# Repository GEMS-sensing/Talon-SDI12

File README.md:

<!--  -->

# Talon-SDI12
Talon daughterboard for [Flight data logger](https://github.com/GEMS-sensing/DFM_-_Flight?tab=readme-ov-file). Designed to interface with [Kestrel](https://github.com/GEMS-sensing/Project-Kestrel) main board. This board is designed to provide data logger with support to interface with [SDI-12 communication standard](https://www.sdi-12.org/current_specification/SDI-12%20Specification%201.4%20February%2020%202023.pdf) for environmental sensors.

# Repo Roadmap
#### [Documents](Documents/) 

General document and image storage for repo and README

#### [Hardware](Hardware/)

Current board files (Eagle), Bill of Materials (BoM), and other design documents

#### [Production](Production/)

Contains the various Gerber and pick and place files required to have the Printed Circuit Boards (PCBs) manufactured or populated 

#### [Software](Software/)

The software associated with the piece of hardware, this is usually diagnostic software used for verifying or investigating the hardware

<!-- #### [Mechanical](Mechanical/)

Mechanical design files and assembly documents -->

<!-- #### [Testing](Testing/)

Scripts and results from the testing process and development process. Contains more detailed information about documented issues among other testing. 
 -->

## Overview
* **Type:** Talon
* **Interfaces:** SDI-12
* **Release Version:** v1.4 - 2022/04/25

<!--  -->

## Features
### On-Board
* SDI-12 ports (x3)
* Dedicated Apogee sensor port (x1)
	* Supports SDI-12 communication and analog voltage input
	* Supports [Apogee pinout standard](https://www.apogeeinstruments.com/apogee-wiring-guide/)
* Port level current limit
	* Custom designed automatic current limit 
	* support for current and voltage measurement for each port
* Data and power control for each port
* Loopback support to perform SDI-12 communication diagnostics 
* EEPROM with UUID built in - can store additional values defined by firmware to track offsets, etc
* ESD protected inputs

<!-- ### Interface
* I<sup>2</sup>C
* M12 circular connector  -->

<!-- <picture>
  <source media="(prefers-color-scheme: dark)" srcset="Documents/Pinout_LIGHT.png">
  
</picture> -->

<!-- ## Specifications
* **Voltage - Supply:** 3.3V
* **Voltage - Logic:** 3.3V
* **Input Current (Avg, 1s period): 30.95&mu;A @ 3.3V**
* **Input Current (Avg, 5s period): 107.43&mu;A @ 3.3V**
* **Input Current (Max): 0.45mA @ 3.3V**

#### Sensor
**Temperature** [^1]
* Range: -40 ~ 125°C 
* Accuracy: &plusmn; 0.2°C
* Repeatability: &plusmn; 0.04°C

**Pressure** [^2]
* Range: 300 ~ 1200 hPa  
* Accuracy: &plusmn; 1 hPa
* Repeatability: &plusmn; 0.06 hPa

**Humidity** [^1]
* Range: 0 ~ 100%
* Accuracy: &plusmn; 2%
* Repeatability: 0.08%

[^1]: [SHT31 Datasheet](https://sensirion.com/media/documents/213E6A3B/63A5A569/Datasheet_SHT3x_DIS.pdf)
[^2]: [DPS368 Datasheet](https://www.infineon.com/dgdl/Infineon-DPS368-DS-v01_00-EN.pdf?fileId=5546d46269e1c019016a0c45105d4b40) -->

<!-- ## Version History

`v0.0` - Initial primal version with screw terminal

`v0.1` - Initial 'hard mount' version, using M12 connector

`v1.0` - Removed pullup select[^3], added logic level buffer and voltage reg on input

`v1.1` - Moved via away from connector pads to prevent bridging when soldering 

`v2.0` - Fixed issue with address select jumper[^3] -->

<!-- ## Jumper Settings 

> [!IMPORTANT]
> Jumper settings valid for version `v2.0` and beyond[^3]

[^3]: See Errata

**Configuration Jumpers**
| Jumper | Purpose | Open | Closed | Default | 
| ------ | ------- | ---------- | ---------- | ----- | 
| `JP1` | I<sup>2</sup>C Address Select | Base Address<sup>&dagger;</sup> | Alt Address<sup>&Dagger;</sup> | Open |

&dagger; SHT31 = `0x44`, DPS368 = `0x76`

&Dagger; SHT31 = `0x44`, DPS368 = `0x77`
 -->

## Known Issues/Errata

None
<!-- #### Solder Jumper Stencil

**Version Affected:** All

**Issue:** Solar input does not support very low impedance sources (e.g. lead acid battery) - see details in issue [#20](https://github.com/GEMS-sensing/Project-Kestrel/issues/20)

**Workaround:** 

* Avoid use of low impedance batteries for input
* Include series impedance to prevent current spikes (not desirable)
* Perform board patch described in issue [#20](https://github.com/GEMS-sensing/Project-Kestrel/issues/20) -->

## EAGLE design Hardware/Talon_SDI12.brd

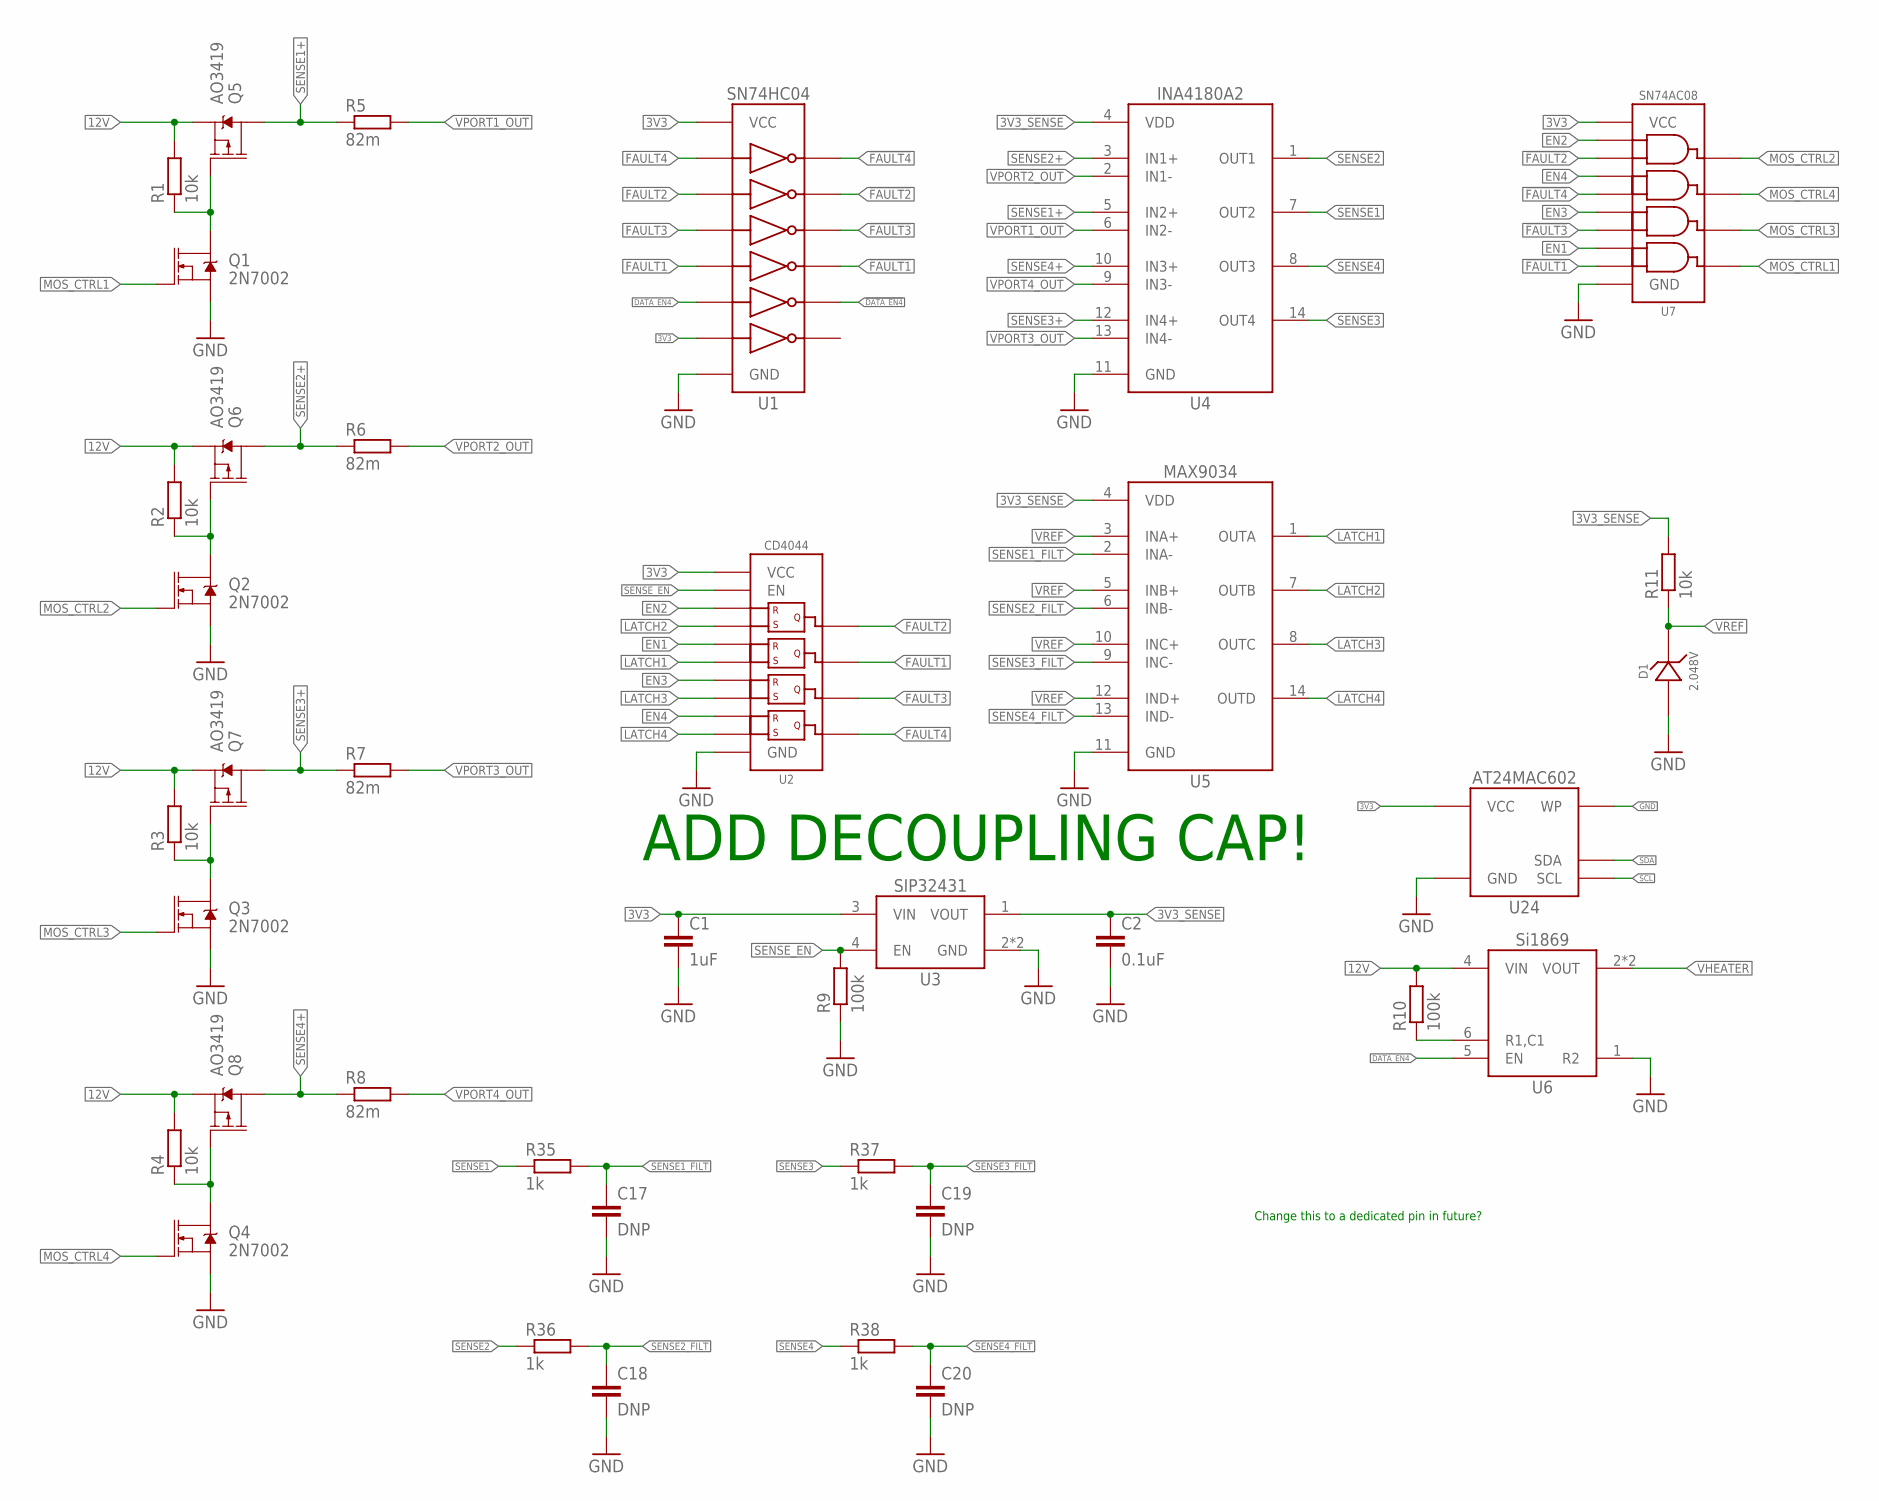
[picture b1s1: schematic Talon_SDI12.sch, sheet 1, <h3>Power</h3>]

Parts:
C1: 1uF; C0603
C2: 0.1uF; C0402
C17, C18, C19, C20: DNP; C0402; MPN DNP; DIGIKEY DNP
D1: 2.048V; SOT23-3
Q1, Q2, Q3, Q4: 2N7002; SOT23-3
Q5, Q6, Q7, Q8: AO3419; SOT23-3
R1, R2, R3, R4, R11: 10k; R0402
R5, R6, R7, R8: 82m; R0603
R9, R10: 100k; R0402
R35, R36, R37, R38: 1k; R0402
U1: SN74HC04; TSSOP14
U2: CD4044; TSSOP16
U3: SIP32431TDFN; TDFN_4
U4: INA4180A2; TSSOP14
U5: MAX9034TSSOP; TSSOP14
U6: SI1869; SC-70_6
U7: SN74AC08; TSSOP14
U24: AT24MAC602SOT23; SOT23-5

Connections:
3V3: C1.1, U1.13 (A6), U1.14 (VCC), U2.16 (VCC), U3.3 (VIN), U7.14 (VCC), U24.4 (VCC); also elsewhere on the board
3V3_SENSE: C2.1, R11.2, U3.1 (VOUT), U4.4 (VDD), U5.4 (VDD)
12V: Q5.2 (S), Q6.2 (S), Q7.2 (S), Q8.2 (S), R1.2, R2.2, R3.2, R4.2, R10.2, U6.4 (VIN); also elsewhere on the board
!DATA_EN4: U1.10 (Y5); also elsewhere on the board
!FAULT1: U1.8 (Y4), U7.13 (B4)
!FAULT2: U1.4 (Y2), U7.2 (B1)
!FAULT3: U1.6 (Y3), U7.10 (B3)
!FAULT4: U1.2 (Y1), U7.5 (B2)
DATA_EN4: U1.11 (A5), U6.5 (EN); also elsewhere on the board
EN1: U2.6 (R2), U7.12 (A4); also elsewhere on the board
EN2: U2.4 (R1), U7.1 (A1); also elsewhere on the board
EN3: U2.12 (R3), U7.9 (A3); also elsewhere on the board
EN4: U2.14 (R4), U7.4 (A2); also elsewhere on the board
FAULT1: U1.9 (A4), U2.9 (Q2); also elsewhere on the board
FAULT2: U1.3 (A2), U2.13 (Q1); also elsewhere on the board
FAULT3: U1.5 (A3), U2.10 (Q3); also elsewhere on the board
FAULT4: U1.1 (A1), U2.1 (Q4); also elsewhere on the board
GND: C1.2, C2.2, C17.2, C18.2, C19.2, C20.2, D1.2 (A), Q1.2 (S), Q2.2 (S), Q3.2 (S), Q4.2 (S), R9.1, U1.7 (GND), U2.8 (GND), U3.2 (GND), U3.EP (GND), U4.11 (GND), U5.11 (GND), U6.1 (R2), U7.7 (GND), U24.2 (GND), U24.5 (WP); also elsewhere on the board
LATCH1: U2.7 (S2), U5.1 (OUTA)
LATCH2: U2.3 (S1), U5.7 (OUTB)
LATCH3: U2.11 (S3), U5.8 (OUTC)
LATCH4: U2.15 (S4), U5.14 (OUTD)
MOS_CTRL1: Q1.1 (G), U7.11 (Y4)
MOS_CTRL2: Q2.1 (G), U7.3 (Y1)
MOS_CTRL3: Q3.1 (G), U7.8 (Y3)
MOS_CTRL4: Q4.1 (G), U7.6 (Y2)
unnamed: Q2.3 (D), Q6.1 (G), R2.1
unnamed: Q1.3 (D), Q5.1 (G), R1.1
unnamed: Q3.3 (D), Q7.1 (G), R3.1
unnamed: Q4.3 (D), Q8.1 (G), R4.1
unnamed: R10.1, U6.6 (R1,C1)
SCL: U24.1 (SCL); also elsewhere on the board
SDA: U24.3 (SDA); also elsewhere on the board
SENSE1: R35.1, U4.7 (OUT2); also elsewhere on the board
SENSE1+: Q5.3 (D), R5.1, U4.5 (IN2+)
SENSE1_FILT: C17.1, R35.2, U5.2 (INA-)
SENSE2: R36.1, U4.1 (OUT1); also elsewhere on the board
SENSE2+: Q6.3 (D), R6.1, U4.3 (IN1+)
SENSE2_FILT: C18.1, R36.2, U5.6 (INB-)
SENSE3: R37.1, U4.14 (OUT4); also elsewhere on the board
SENSE3+: Q7.3 (D), R7.1, U4.12 (IN4+)
SENSE3_FILT: C19.1, R37.2, U5.9 (INC-)
SENSE4: R38.1, U4.8 (OUT3); also elsewhere on the board
SENSE4+: Q8.3 (D), R8.1, U4.10 (IN3+)
SENSE4_FILT: C20.1, R38.2, U5.13 (IND-)
SENSE_EN: R9.2, U2.5 (EN), U3.4 (EN); also elsewhere on the board
VHEATER: U6.2 (VOUT), U6.3 (VOUT); also elsewhere on the board
VPORT1_OUT: R5.2, U4.6 (IN2-); also elsewhere on the board
VPORT2_OUT: R6.2, U4.2 (IN1-); also elsewhere on the board
VPORT3_OUT: R7.2, U4.13 (IN4-); also elsewhere on the board
VPORT4_OUT: R8.2, U4.9 (IN3-); also elsewhere on the board
VREF: D1.1 (C), R11.1, U5.3 (INA+), U5.5 (INB+), U5.10 (INC+), U5.12 (IND+)

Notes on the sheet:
ADD DECOUPLING CAP!
Change this to a dedicated pin in future?

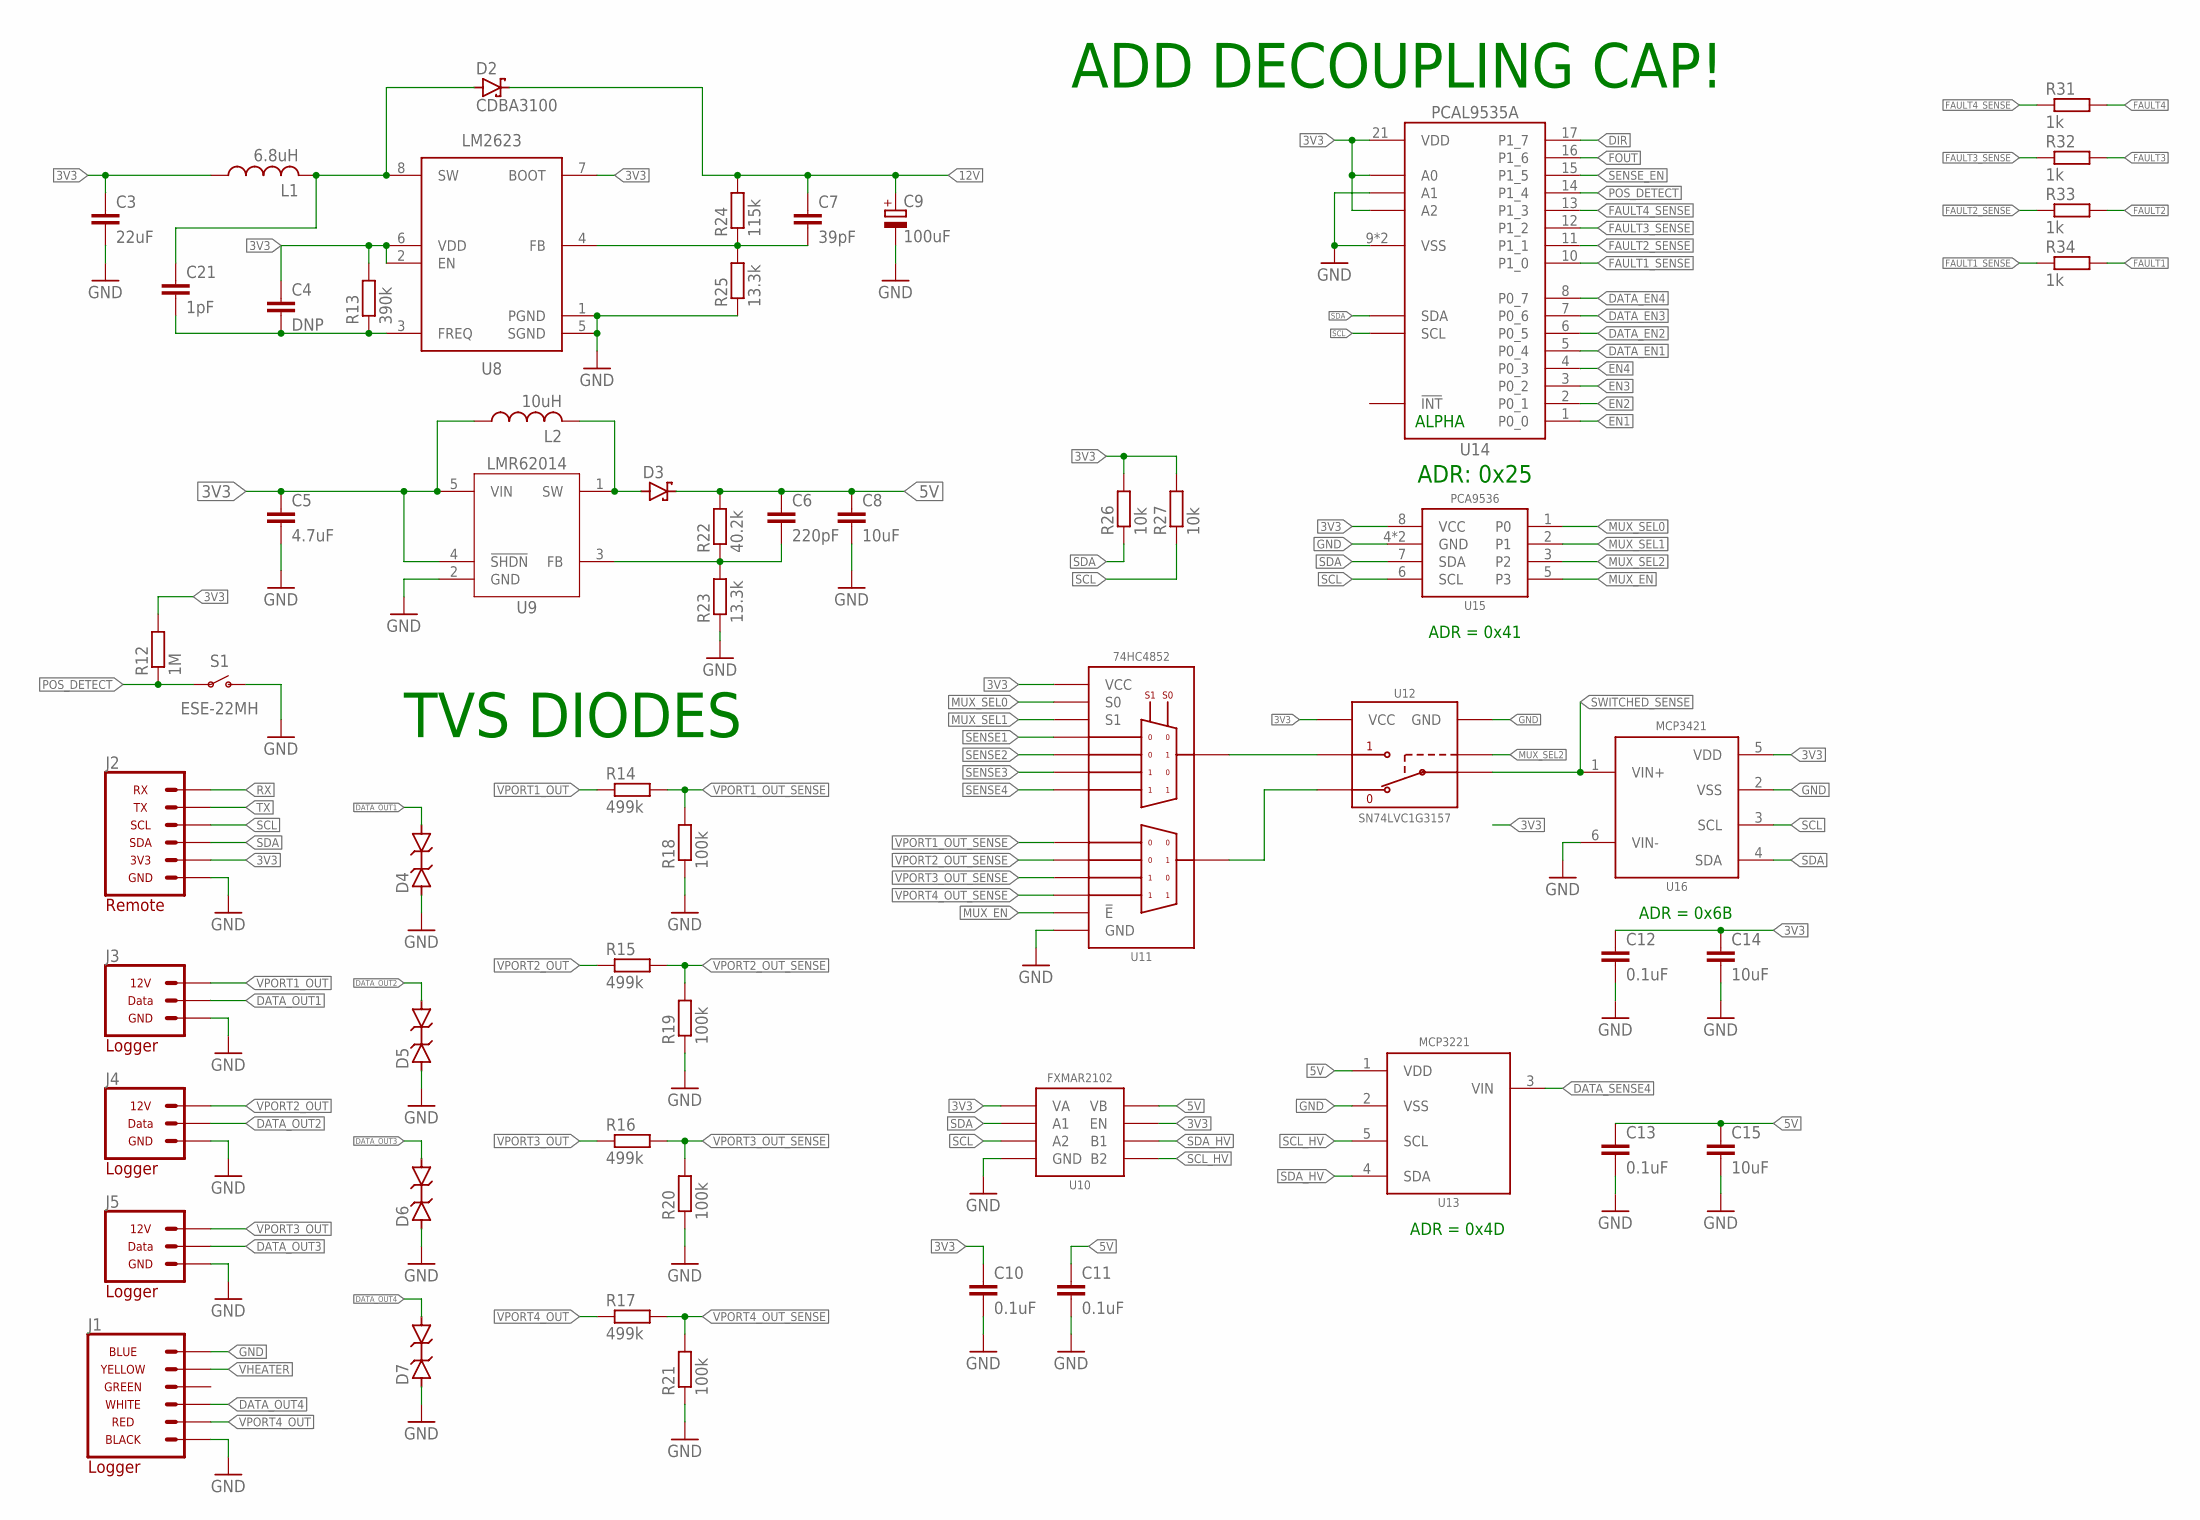
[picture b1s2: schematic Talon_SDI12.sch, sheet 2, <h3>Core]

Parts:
C3: 22uF; C0805
C4: DNP; C0402; MPN DNP; DIGIKEY DNP
C5: 4.7uF; C0805
C6: 220pF; C0603
C7: 39pF; C0402
C8: 10uF; C0805; MPN TMK212BBJ106KG-T; DIGIKEY 587-2985-1-ND
C9: 100uF; C2917; MPN 293D107X0016D2TE3; DIGIKEY 718-293D107X0016D2TE3CT-ND
C10, C11, C12, C13: 0.1uF; C0402
C14, C15: 10uF; C0805
C21: 1pF; C0402
D2: CDBA3100; DO214AC; MPN CDBA3100-HF; DIGIKEY 641-1747-1-ND
D3: DIODE_SCHOTTKYSOD-123; SOD-123; MPN MBR0520LT1G; DIGIKEY MBR0520LT1GOSCT-ND
D4, D5, D6, D7: 12V; D0402; MPN D12V0L1B2LP-7B; DIGIKEY D12V0L1B2LP-7BDICT-ND
J1: CONN_APOGEE_LOGGER; 1X06_M8_PHOENIX_1456022_BOARDLOCK
J2: CONN_TALON_REMOTE; 1X06_MICROLOCKPLUS
J3, J4, J5: CONN_SDI-12_LOGGERM8_TE_BOARDLOCK; 1X03_M8_TE_T40410_BOARDLOCK
L1: 6.8uH; WE-MAIA(4.1X4.1); MPN 78438357068; DIGIKEY 732-11744-1-ND
L2: 10uH; 1008; MPN 74438323100; DIGIKEY 732-4851-1-ND
R12: 1M; R0402
R13: 390k; R0603
R14, R15, R16, R17: 499k; R0603
R18, R19, R20, R21: 100k; R0402
R22: 40.2k; R0603
R23, R25: 13.3k; R0603
R24: 115k; R0603
R26, R27: 10k; R0402
R31, R32, R33, R34: 1k; R0402
S1: ESE-22MH
U8: LM2621; DGK_S-PDSO-G8; MPN LM2623AMM/NOPB; DIGIKEY LM2623AMM/NOPBCT-ND
U9: LMR62014SOT23; DBV0005A
U10: FXMAR2102UMLP; UQFN-8_1.4X1.2
U11: 74HC4852; VQFN-16
U12: SN74LVC1G3157SC70; DCK_R-PDSO-G6
U13: MCP3221; SOT23-5
U14: PCAL9535AQFN; QFN24
U15: PCA9536DFN; DFN_8_3X3
U16: MCP3421A3; SOT23-6L

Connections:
3V3: C3.1, C4.1, C5.1, C10.1, C12.1, C14.1, J2.2 (3V3), L1.P$1 (1), L2.1, R12.2, R13.2, R26.2, R27.2, U8.2 (EN), U8.6 (VDD), U8.7 (BOOT), U9.4 (!SHDN), U9.5 (VIN), U10.1 (VA), U10.5 (EN), U11.16 (VCC), U12.5 (VCC), U14.18 (A0), U14.21 (VDD), U14.24 (A2), U15.8 (VCC), U16.5 (VDD); also elsewhere on the board
5V: C6.1, C8.1, C11.1, C13.1, C15.1, D3.CAT (C), R22.2, U10.8 (VB), U13.1 (VDD); also elsewhere on the board
12V: C7.1, C9.+, D2.C, R24.2; also elsewhere on the board
DATA_EN1: U14.5 (P0_4); also elsewhere on the board
DATA_EN2: U14.6 (P0_5); also elsewhere on the board
DATA_EN3: U14.7 (P0_6); also elsewhere on the board
DATA_EN4: U14.8 (P0_7); also elsewhere on the board
DATA_OUT1: D4.2 (C), J3.4 (DATA); also elsewhere on the board
DATA_OUT2: D5.2 (C), J4.4 (DATA); also elsewhere on the board
DATA_OUT3: D6.2 (C), J5.4 (DATA); also elsewhere on the board
DATA_OUT4: D7.2 (C), J1.3; also elsewhere on the board
DATA_SENSE4: U13.3 (VIN); also elsewhere on the board
DIR: U14.17 (P1_7); also elsewhere on the board
EN1: U14.1 (P0_0); also elsewhere on the board
EN2: U14.2 (P0_1); also elsewhere on the board
EN3: U14.3 (P0_2); also elsewhere on the board
EN4: U14.4 (P0_3); also elsewhere on the board
FAULT1: R34.2; also elsewhere on the board
FAULT1_SENSE: R34.1, U14.10 (P1_0)
FAULT2: R33.2; also elsewhere on the board
FAULT2_SENSE: R33.1, U14.11 (P1_1)
FAULT3: R32.2; also elsewhere on the board
FAULT3_SENSE: R32.1, U14.12 (P1_2)
FAULT4: R31.2; also elsewhere on the board
FAULT4_SENSE: R31.1, U14.13 (P1_3)
FOUT: U14.16 (P1_6); also elsewhere on the board
GND: C3.2, C5.2, C8.2, C9.-, C10.2, C11.2, C12.2, C13.2, C14.2, C15.2, D4.1 (A), D5.1 (A), D6.1 (A), D7.1 (A), J1.1, J1.6, J2.1 (GND), J3.3 (GND), J4.3 (GND), J5.3 (GND), R18.1, R19.1, R20.1, R21.1, R23.1, R25.1, S1.1 (O), U8.1 (PGND), U8.5 (SGND), U9.2 (GND), U10.4 (GND), U11.8 (GND), U11.EP (GND), U12.2 (GND), U13.2 (VSS), U14.9 (VSS), U14.23 (A1), U14.EP (VSS), U15.4 (GND), U15.EP (GND), U16.2 (VSS), U16.6 (VIN-); also elsewhere on the board
MUX_EN: U11.6 (!E), U15.5 (P3); also elsewhere on the board
MUX_SEL0: U11.10 (S0), U15.1 (P0)
MUX_SEL1: U11.9 (S1), U15.2 (P1)
MUX_SEL2: U12.6 (S), U15.3 (P2)
unnamed: C4.2, C21.2, R13.1, U8.3 (FREQ)
unnamed: C21.1, D2.A, L1.P$2 (2), U8.8 (SW)
unnamed: C7.2, R24.1, R25.2, U8.4 (FB)
unnamed: C6.2, R22.1, R23.2, U9.3 (FB)
unnamed: U11.3 (2Z), U12.3 (B1)
unnamed: U11.13 (1Z), U12.1 (B2)
POS_DETECT: R12.1, S1.2, U14.14 (P1_4)
RX: J2.6 (RX); also elsewhere on the board
SCL: J2.4 (SCL), R27.1, U10.3 (A2), U14.19 (SCL), U15.6 (SCL), U16.3 (SCL); also elsewhere on the board
SCL_HV: U10.6 (B2), U13.5 (SCL)
SDA: J2.3 (SDA), R26.1, U10.2 (A1), U14.20 (SDA), U15.7 (SDA), U16.4 (SDA); also elsewhere on the board
SDA_HV: U10.7 (B1), U13.4 (SDA)
SENSE1: U11.12 (1Y0); also elsewhere on the board
SENSE2: U11.14 (1Y1); also elsewhere on the board
SENSE3: U11.15 (1Y2); also elsewhere on the board
SENSE4: U11.11 (1Y3); also elsewhere on the board
SENSE_EN: U14.15 (P1_5); also elsewhere on the board
SW1: D3.ANODE (A), L2.2, U9.1 (SW)
SWITCHED_SENSE: U12.4 (A), U16.1 (VIN+)
TX: J2.5 (TX); also elsewhere on the board
VHEATER: J1.5; also elsewhere on the board
VPORT1_OUT: J3.1 (12V), R14.1; also elsewhere on the board
VPORT1_OUT_SENSE: R14.2, R18.2, U11.1 (2Y0)
VPORT2_OUT: J4.1 (12V), R15.1; also elsewhere on the board
VPORT2_OUT_SENSE: R15.2, R19.2, U11.5 (2Y1)
VPORT3_OUT: J5.1 (12V), R16.1; also elsewhere on the board
VPORT3_OUT_SENSE: R16.2, R20.2, U11.2 (2Y2)
VPORT4_OUT: J1.2, R17.1; also elsewhere on the board
VPORT4_OUT_SENSE: R17.2, R21.2, U11.4 (2Y3)

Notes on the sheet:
ALPHA
ADD DECOUPLING CAP!
TVS DIODES
ADR: 0x25
ADR = 0x6B
ADR = 0x4D
ADR = 0x41

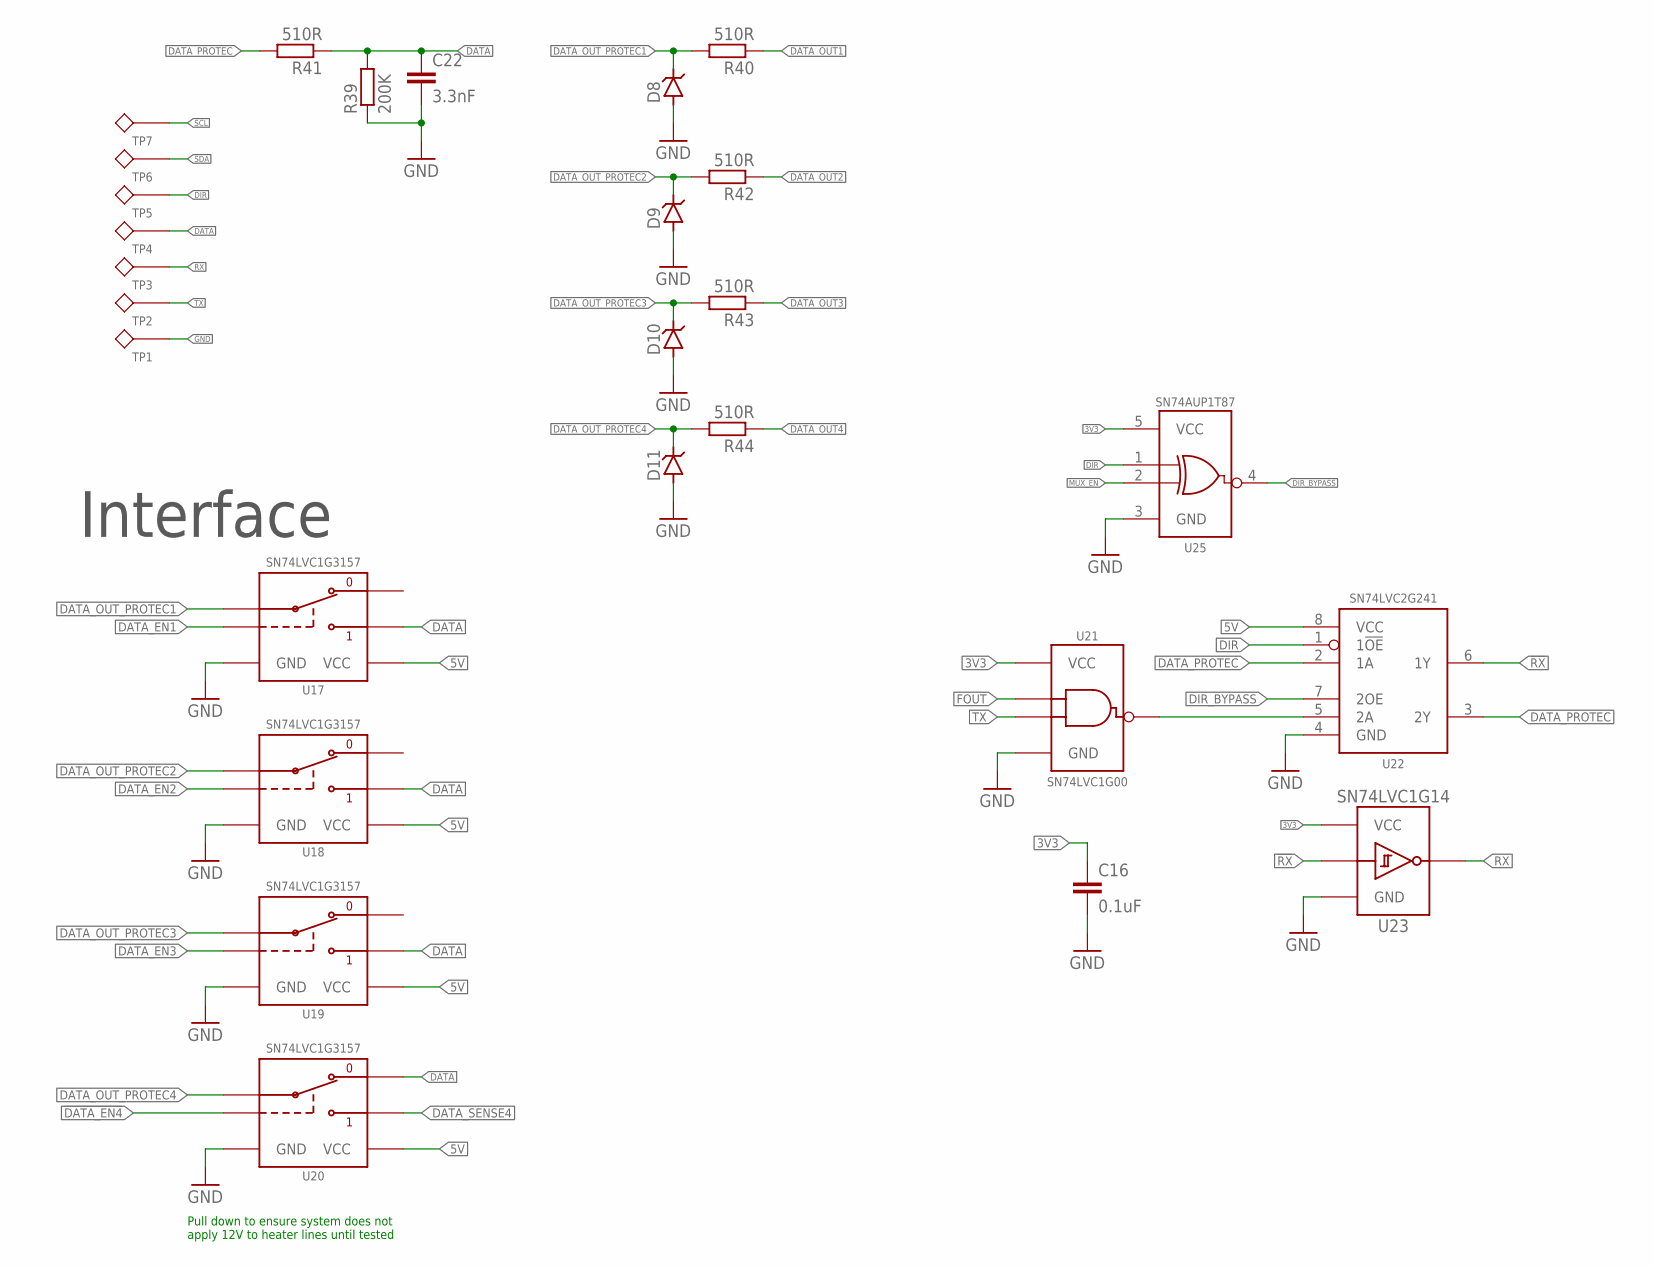
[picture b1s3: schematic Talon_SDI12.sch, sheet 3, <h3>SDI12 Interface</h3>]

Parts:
C16: 0.1uF; C0402
C22: 3.3nF; C0402
D8, D9, D10, D11: DIODE_ZENERSOD-323; SOD323-R; MPN BZX384B5V1-HE3-08; DIGIKEY BZX384B5V1-HE3-08GICT-ND
R39: 200K; R0402
R40, R41, R42, R43, R44: 510R; R0402
TP1, TP2, TP3, TP4, TP5, TP6, TP7: TESTPOINTRCU; TESTPOINT_0603
U17, U18, U19, U20: SN74LVC1G3157SC70; DCK_R-PDSO-G6
U21: SN74LVC1G00SC70; DCK_R-PDSO-G5
U22: SN74LVC2G241DCU; DCU_(R-PDSO-G8)
U23: SN74LVC1G14DCK; DCK_R-PDSO-G5
U25: SN74AUP1T87; DCK_R-PDSO-G5

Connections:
3V3: C16.1, U21.5 (VCC), U23.5 (VCC), U25.5 (VCC); also elsewhere on the board
5V: U17.5 (VCC), U18.5 (VCC), U19.5 (VCC), U20.5 (VCC), U22.8 (VCC); also elsewhere on the board
!DATA_EN4: U20.6 (S); also elsewhere on the board
!RX: U22.6 (1Y), U23.2 (A)
DATA: C22.1, R39.2, R41.1, TP4.1, U17.1 (B2), U18.1 (B2), U19.1 (B2), U20.3 (B1)
DATA_EN1: U17.6 (S); also elsewhere on the board
DATA_EN2: U18.6 (S); also elsewhere on the board
DATA_EN3: U19.6 (S); also elsewhere on the board
DATA_OUT1: R40.1; also elsewhere on the board
DATA_OUT2: R42.1; also elsewhere on the board
DATA_OUT3: R43.1; also elsewhere on the board
DATA_OUT4: R44.1; also elsewhere on the board
DATA_OUT_PROTEC1: D8.C, R40.2, U17.4 (A)
DATA_OUT_PROTEC2: D9.C, R42.2, U18.4 (A)
DATA_OUT_PROTEC3: D10.C, R43.2, U19.4 (A)
DATA_OUT_PROTEC4: D11.C, R44.2, U20.4 (A)
DATA_PROTEC: R41.2, U22.2 (1A), U22.3 (2Y)
DATA_SENSE4: U20.1 (B2); also elsewhere on the board
DIR: TP5.1, U22.1 (1!OE), U25.1 (A); also elsewhere on the board
DIR_BYPASS: U22.7 (2OE), U25.4 (Y)
FOUT: U21.1 (A); also elsewhere on the board
GND: C16.2, C22.2, D8.A, D9.A, D10.A, D11.A, R39.1, TP1.1, U17.2 (GND), U18.2 (GND), U19.2 (GND), U20.2 (GND), U21.3 (GND), U22.4 (GND), U23.3 (GND), U25.3 (GND); also elsewhere on the board
MUX_EN: U25.2 (B); also elsewhere on the board
unnamed: U21.4 (Y), U22.5 (2A)
RX: TP3.1, U23.4 (Y); also elsewhere on the board
SCL: TP7.1; also elsewhere on the board
SDA: TP6.1; also elsewhere on the board
TX: TP2.1, U21.2 (B); also elsewhere on the board

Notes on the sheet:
Interface
Pull down to ensure system does not apply 12V to heater lines until tested

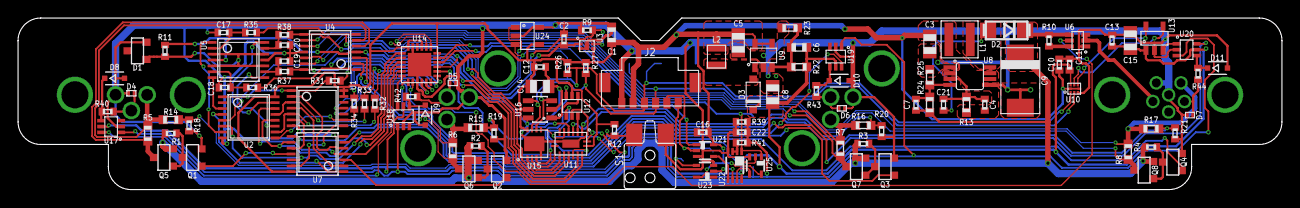
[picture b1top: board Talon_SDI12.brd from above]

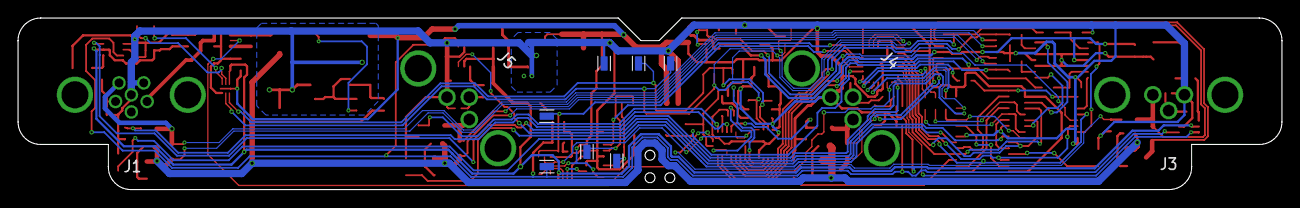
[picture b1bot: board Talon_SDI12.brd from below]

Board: 2 copper layers, 140.0 x 19.0 mm, 122 parts (11 on the bottom side), 97 nets.

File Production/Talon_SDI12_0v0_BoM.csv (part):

"Qty","Value","Device","Package","Parts","Description","DIGIKEY","DISP","MF","MPN","VALUE","VALUE_PART",
"1","","DIODE_SCHOTTKYSOD-123","SOD-123","D3","Generic Shottky Diode","MBR0520LT1GOSCT-ND","","ON Semiconductor","MBR0520LT1G","","",
"7","0.1uF","C-EU0.1UFC0402","C0402","C2, C4, C10, C11, C12, C13, C16","CAPACITOR, European symbol","490-4759-1-ND","","Murata","GCM155R71C104KA55D","","",
"3","100k","R-EU_100KR0402","R0402","R9, R10, R30","RESISTOR, European symbol","311-100KLRCT-ND","","Yageo","RC0402FR-07100KL","","100k",
"4","100k","R-EU_100KR0603","R0603","R18, R19, R20, R21","RESISTOR, European symbol","311-100KHRCT-ND","","Yageo","RC0603FR-07100KL","","100k",
"7","10k","R-EU_10KR0402","R0402","R1, R2, R3, R4, R11, R26, R27","RESISTOR, European symbol","311-10.0KLRCT-ND","","Yageo","RC0402FR-0710KL","","10k",
"2","10uF","C-EU10UFC0805","C0805","C14, C15","CAPACITOR, European symbol","490-6473-1-ND","","Murata","GRM21BR61C106KE15K","","",
"1","10uF","C-EU10UFC0805","C0805","C8","CAPACITOR, European symbol","587-2985-1-ND","","Taiyo Yuden","TMK212BBJ106KG-T","","",
"1","10uH","INDUCTOR_1008","1008","L2","Genaric Inductor","732-4851-1-ND","","Wurth","74438323100","","",
"1","110k","R-EU_110KR0603","R0603","R28","RESISTOR, European symbol","CR0603-FX-1103ELFCT-ND","","Bourns","CR0603-FX-1103ELF","","110k",
"1","115k","R-EU_115KR0603","R0603","R24","RESISTOR, European symbol","311-115KHRCT-ND","","Yageo","RC0603FR-07115KL","","115k",
"2","13.3k","R-EU_13.3KR0603","R0603","R23, R25","RESISTOR, European symbol","311-13.3KHRCT-ND","","Yageo","RC0603FR-0713K3L","","13.3k",
"1","1M","R-EU_1MR0402","R0402","R12","RESISTOR, European symbol","311-1.00MLRCT-ND","","Yageo","RC0402FR-071ML","","1M",
"1","1uF","C-EU1UFC0603","C0603","C1","CAPACITOR, European symbol","587-1251-1-ND","","Yaiyo Yuden","EMK107BJ105KA-T","","",
"1","2.048V","LM40402.048","SOT23-3","D1","LM4040 - Precision Micropower Shunt Voltage Referance","LM4040CIM3-2.0/NOPBCT-ND","","TI","LM4040CIM3-2.0/NOPB","","",
"1","220pF","C-EU220PFC0603","C0603","C6","CAPACITOR, European symbol","399-1066-1-ND","","Kemet","C0603C221J5GACTU","","",
"1","22uF","C-EU22UFC0805","C0805","C3","CAPACITOR, European symbol","490-9952-1-ND","","Murata","GRM219R61C226ME15L","","",
"4","2N7002","MOSFET-NCH-2N7002P","SOT23-3","Q1, Q2, Q3, Q4","N-channel MOSFET","1727-4692-1-ND","","Nexperia","2N7002P","215","2N7002",
"1","39pF","C-EU39PFC0402","C0402","C7","CAPACITOR, European symbol","399-1018-1-ND","","Kemet","C0402C390J5GAC7867","","",
"1","4.7uF","C-EU4.7UFC0805","C0805","C5","CAPACITOR, European symbol","399-7415-1-ND","","Kemet","C0805C475K4RACTU","","",
"1","40.2k","R-EU_40.2KR0603","R0603","R22","RESISTOR, European symbol","RMCF0603FT40K2CT-ND","","Stackpole","RMCF0603FT40K2","","40.2k",
"1","470k","R-EU_470KR0603","R0603","R13","RESISTOR, European symbol","311-470KGRCT-ND","","Yageo","RC0603JR-07470KL","","470k",
"1","49.9k","R-EU_49.9KR0603","R0603","R29","RESISTOR, European symbol","RMCF0603FG49K9CT-ND","","Stackpole","RMCF0603FG49K9","","49.9k",
"4","499k","R-EU_499KR0603","R0603","R14, R15, R16, R17","RESISTOR, European symbol","311-499KHRCT-ND","","Yageo","RC0603FR-07499KL","","499k",
"1","6.8uH","INDUCTOR_MAIA_4.1X4.1","WE-MAIA(4.1X4.1)","L1","Genaric Inductor","732-11744-1-ND","","Wurth","78438357068","","",
"1","68uF","CTANT_EU2917","C2917","C9","Genaric Tantalum Capacitor","399-3803-1-ND","","Kemet","T491D686K020AT","","",
"4","6V","DIODE_ESD_BI_D5V0L1_0402","D0402","D4, D5, D6, D7","Generic Bidirectional ESD Diode","D5V0L1B2LP4-7BDICT-ND","","Diodes Inc","D5V0L1B2LP4-7B","6V","",
"1","74HC4852","74HC4852","VQFN-16","U11","74HC4852  - Analog Multiplexer, Dual 4-Channel (1:4 x 2)","1727-7953-1-ND","74HC4852","Nexperia","74HC4852BQ-Q100","11","",
"4","82m","R-EU_0.082R0603","R0603","R5, R6, R7, R8","RESISTOR, European symbol","408-1446-1-ND","","Susumu","RL0816T-R082-F","","82m",
"4","AO3419","MOSFET-PCH-AO3419","SOT23-3","Q5, Q6, Q7, Q8","P-channel MOSFET","785-1013-1-ND","","Alpha and Omega","AO3419","AO3419","",
"1","CD4044","CD4044","TSSOP16","U2","CD404x  - S-R Latch, Quad","296-31499-1-ND","CD4044","TI","CD4044BPWR","","",
"1","CDBA3100","DIODE_SCHOTTKYDO-214AC","DO214AC","D2","Generic Shottky Diode","641-1747-1-ND","","Comchip","CDBA3100-HF","","",
"1","CONN_APOGEE_LOGGER","CONN_APOGEE_LOGGER","1X06_M8_PHOENIX_1456022_BOARDLOCK","J1","GEMS Connector for Apogee Devices","277-17111-ND","Logger","Phoenix Contact","1456022","","",
"3","CONN_SDI-12_LOGGERM8_TE_BOARDLOCK","CONN_SDI-12_LOGGERM8_TE_BOARDLOCK","1X03_M8_TE_T40410_BOARDLOCK","J3, J4, J5","SDI-12 Connector","A126811-ND","Logger","TE Connectivity","T4041037031-000","","",
"1","CONN_TALON_REMOTE","CONN_TALON_REMOTE","1X06_MICROLOCKPLUS","J2","GEMS Connector for Talon Interface","900-2059570671CT-ND","Remote","Molex","2059570671","","",
"1","ESE-22MH","SPSTESE-22MH","ESE-22MH","S1","Generic SPST (Single Pole Single Throw) Switch","P13584SCT-ND","","Panasonic","ESE-22MH24","ESE-22MH","",
"1","FXMAR2102UMLP","FXMAR2102UMLP","UQFN-8_1.4X1.2","U10","FXMAR2102 - 2 Channel Bidirectional Voltage Level Translator for I2C Applications","FXMAR2102UMX-F106CT-ND","FXMAR2102","OnSemi","FXMAR2102UMX-F106","","",
"1","INA4180A2","INA4180A2","TSSOP14","U4","INA4180 - Analog Output Current Sense Amplifier","296-49095-1-ND","INA4180A2","TI","INA4180A2IPWR","","",
"1","LM2621","LM2621","DGK_S-PDSO-G8","U8","LM2621 - Low Input Voltage, Step-Up DC-DC Converter","LM2621MMX/NOPBCT-ND","LM2621","TI","LM2621MMX/NOPB","","",
"1","LMR62014SOT23","LMR62014SOT23","DBV0005A","U9","LMR62014 - Step-Up Boost Regulator","LMR62014XMF/NOPBCT-ND","LMR62014","TI","LMR62014XMF/NOPB","","",
"1","MAX9034TSSOP","MAX9034TSSOP","TSSOP14","U5","MAX9034 - Ultra-Small nanoPower Single Comparator , Quad","MAX9034AUD+CT-ND","MAX9034","Maxim","MAX9034AUD+T","","",
"1","MCP23018QFN","MCP23018QFN","QFN24","U14","MCP23018 - I2C I/O Expander, 16 bit wtih interrupt and reset","MCP23018T-E/MJCT-ND","","TI","MCP23018T-E/MJ","","",
"1","MCP3221","MCP3221","SOT23-5","U13","MCP342* - SAR ADC","MCP3221A5T-I/OTCT-ND","MCP3221","TI","MCP3221A5T-I/OT","","",
"1","MCP3421A3","MCP3421A3","SOT23-6L","U16","MCP342* - Sigma Delta ADC","MCP3421A3T-E/CHCT-ND","MCP3421","Microchip","MCP3421A3T-E/CH","","",
"1","PCA9536DFN","PCA9536DFN","DFN_8_3X3","U15","PCA9536 - I2C I/O Expander, 4 bit, 5V tollerant","568-4079-1-ND","","NXP","PCA9536TK","118","",
"1","SI1869","SI1869","SC-70_6","U6","Si1869 - Ultra Low Leakage Load Switch with Level Shift","SI1869DH-T1-E3CT-ND","Si1869","Vishay","SI1869DH-T1-E3","","",
"1","SIP32431TDFN","SIP32431TDFN","TDFN_4","U3","SiP3243x - Ultra Low Leakage Load Switch with Reverse Blocking","SIP32431DNP3-T1GE4CT-ND","SIP32431","Vishay","SIP32431DNP3-T1GE4","","",
"1","SN74AC08","SN74AC08","TSSOP14","U7","SN74AC08 - AND, 4 Element, 2 Input","296-4292-1-ND","","TI","SN74AC08PWR","","",
"1","SN74AUP1T157DCK","SN74AUP1T157DCK","DCK_R-PDSO-G6","U12","SN74AUP1T157  - Non-Inverting Digital Multiplexer, Schmitt Trigger (1:2)","296-27393-1-ND","SN74AUP1T157","TI","SN74AUP1T157DCKR","","",
"1","SN74HC04","SN74HC04","TSSOP14","U1","SN74HC04 - NOT, 4 Element, 1 Input - Hex Inverter","296-8208-1-ND","","TI","SN74HC04PWR","","",
"1","SN74LVC1G00SC70","SN74LVC1G00SC70","DCK_R-PDSO-G5","U21","","296-9846-1-ND","SN74LVC1G00","","SN74LVC1G00DCKR","","",
"1","SN74LVC1G17DCK","SN74LVC1G17DCK","DCK_R-PDSO-G5","U23","SN74LVC1G17 - Single Schmitt Trigger Logic Buffer","296-11934-1-ND","SN74LVC1G17","TI","SN74LVC1G17DCKR","","",
"4","SN74LVC1G3157SC70","SN74LVC1G3157SC70","DCK_R-PDSO-G6","U17, U18, U19, U20","SN74LVC1G3157 - SPDT Analog Switch","296-14909-1-ND","SN74LVC1G3157","TI","SN74LVC1G3157DCKR","","",
"1","SN74LVC2G241DCU","SN74LVC2G241DCU","DCU_(R-PDSO-G8)","U22","SN74LVC2G241 - Dual Buffer and Driver with 3-State Outputs","296-32323-1-ND","","TI","SN74LVC2G241DCUT","","",
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
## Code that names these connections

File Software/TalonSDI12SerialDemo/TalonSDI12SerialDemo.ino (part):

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const uint8_t RX = 0;

//IO Expander Pins
const uint8_t FOut = 14;
const uint8_t Dir = 15;

const uint8_t POS_DETECT = 12;
const uint8_t SENSE_EN = 13;

const uint8_t DATA_EN1 = 4;
const uint8_t EN1 = 0;
const uint8_t FAULT1 = 8;

//Configured for pins on the Particle Boron
//const uint8_t EXT_EN = 8;
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PCA9536 ioSense;

//IO Sense pins
const uint8_t MUX_EN = 3;
const uint8_t MUX_SEL0 = 0;
const uint8_t MUX_SEL1 = 1;
const uint8_t MUX_SEL2 = 2;

const float VoltageDiv = 6; //Program voltage divider
const float CurrentDiv = 0.243902439; //82mOhm, 50V/V Amp
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 //  	io.digitalWritePort(0, ALL_HIGH);
	pinMode(TX, OUTPUT); //DEBUG1!

	// io.pinPullup(0, DATA_EN1, PU_ENABLE);
	// io.pinPullup(0, DATA_EN2, PU_ENABLE);
	// io.pinPullup(0, DATA_EN3, PU_ENABLE);
	// io.pullUp(DATA_EN1, true);
	// io.pullUp(DATA_EN2, true);
	// io.pullUp(DATA_EN3, true);

	// io.pinMode(0, DATA_EN1, OUTPUT);
	// io.pinMode(0, DATA_EN2, OUTPUT);
	// io.pinMode(0, DATA_EN3, OUTPUT);

	// io.digitalWrite( DATA_EN1, HIGH);
	// io.digitalWrite( DATA_EN2, HIGH);
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
	// io.pullUp(FOut, true);
	// io.pullUp(Dir, true);
	// io.pinPullup(0, FOut, true);
	// io.pinPullup(0, Dir, true);
	// io.pinMode(0, FOut, OUTPUT);
	// io.pinMode(0, Dir, OUTPUT);
	io.pinMode( Dir, OUTPUT); //Set to output 
	io.pinMode( FOut, OUTPUT); //Set to output 
	io.digitalWrite( Dir, HIGH); //Set to transmit 
//  io.digitalWrite( FOut, LOW); //DEBUG!
	Serial1.begin(1200, SERIAL_7E1);
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
void loop() {
	// io.pinMode(0, TX, LOW);
	// io.pinMode(0, FOut, LOW);
	// delay(1000);
	// io.pinMode(0, FOut, LOW);
	// io.pinMode(0, TX, HIGH);
	// delay(1000);
	// io.pinMode(0, FOut, HIGH);
	// io.pinMode(0, TX, LOW);
	// delay(1000);
	// io.pinMode(0, FOut, HIGH);
	// io.pinMode(0, TX, HIGH);
	// delay(1000);
	static int ReadLength = 0;
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void SendBreak()
{
	// io.pinMode(0, Dir, OUTPUT); //Make sure direction is set to output
	// io.pinMode(0, FOut, OUTPUT); //Make sure the force out pin is in output mode
	io.digitalWrite( Dir, HIGH); //Set direction to output
	io.digitalWrite( FOut, LOW); //Set low to force output high
	delay(13); //Wait for bus to acnowledge action
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void SetDefaultPins()
{
	Serial.println(io.begin()); //DEBUG!
	io.pinMode(SENSE_EN, OUTPUT); //Set sense control as output
	io.digitalWrite(SENSE_EN, HIGH); //Default sense to on - NOTE: For proper sequencing, this must be done BEFORE each enable line is driven high
	for(int i = 0; i < 8; i++) { //Enable all power, then all data
		io.pinMode(i, OUTPUT); 
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		io.pinMode(i, INPUT_PULLUP);
	}

	io.pinMode(POS_DETECT, INPUT); //Set position detect as normal pullup (has external pullup)
	// io.pinMode(SENSE_EN, OUTPUT); //Set sense control as output
	// io.digitalWrite(SENSE_EN, HIGH); //Default sense to on 
}

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
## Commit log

2021-10-01 Initial layout complete
2021-10-08 Layout and cleanup done, review needed
2021-10-12 Layout, gerbers, and BoM for v0.0 - submitted to fab
2021-10-14 V0.1 Updates - Added EEPROM
2021-10-14 Generated documentation for v0.1 quote
2021-10-21 Added alpha testing firmware
2021-10-22 Updated demo to support aux voltage sensor
2021-11-22 Updated v1.0, sent to fab
    Made fixes for v1.0:
    - Fixed bypass control
    - Changed arrangement of 12V reg
    - Added filter lines (clitch protection) to sense lines
    - Flipped Talon connector port pinout
    - Adjusted port 4 topology to deal with pulldown issue
2021-11-23 Updated paste layout
2021-11-23 v1.1 Updates
    moved port 1 and port 4, sent to fab
2021-12-10 Added v1.1 BoM
2021-12-10 Added v1.1 mechanical files
2021-12-10 v1.2 updates
    Fixed physical overlap in current limit circuit
2022-02-18 Added v1.2 BoM, corrected demo interface
2022-02-25 v1.3 Updates
2022-02-25 Added .ods to gitignore
2022-03-30 Added license
2022-04-06 Updates for BoM
2022-04-06 Added mount file
2022-04-06 Updated EEPROM part number
2022-04-22 Updated to v1.4
    Added loopback functionality, replaced MCP23018 with PACL9535A, fixed inverter (U23) model, fixed attributes on schematics
2022-04-25 Added gerbers for v1.5
2022-04-25 Added gerbers for v1.4
2024-09-01 Updated README and board images
2024-11-02 Added production info

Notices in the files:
parts and their libraries:
bschulz: This work is licensed under the Creative Commons Attribution-ShareAlike 4.0
http://creativecommons.org/licenses/by-sa/4.0
